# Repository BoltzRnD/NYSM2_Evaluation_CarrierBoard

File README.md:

# NYSM.2 Evaluation Carrier Board

### Note - This repository hosts the design files for the evaluation carrier board only, to explore the NYSM.2 Stepper Driver module please refer to NYSM.2 repository here -
<a href="https://github.com/BoltzRnD/NYSM2_Open_Stepper_Standard">NYSM.2 Open Modular Stepper Driver Interface Standard by Boltz R&D </a>
</br>

### Join our Discord Server to Discuss NYSM.2 -

# NYSM.2 Open Stepper Standard
## Not Your Standard M.2
### "Not Your Standard M.2" is literally not your standard m.2 interface, and is a new open-source stepper motor driver board that utilizes the M.2 interface to control motors using the TMCxx and all other stepper drivers.

Modular stepper drivers are far superior than traditional pololu footprints as it has

1. Poka-yoke installations: The Key's in the interfaces makes sure that you never mess up installation orientations of the driver

apart from this NYSM.2 extends beyond these to provide more features as below:

1. physical locking mechanisms: to make sure drivers are locked in when In operation.

2. Horizontal installation: instead of vertical mounting, to not only save space in Z axis, but to also make the system less fragile to accidental damage if stuck by a physical shock.

3. Top and Bottom Installations: since NYSM.2 utilizes SMD and single layer mounted connectors, it means that it is possible to add by design 2 NYSM.2 modules in the same footprint area, drastically reducing the required footprint for more drivers - i.e - 20 drivers in 10 drivers area by installing 10 on top layer and 10 on bottom.

4. highly cost effective: since M.2 is a widely available standard with high MOQs already flooding the industry, the M.2 connectors can be integrated at very low costs into your design, where the stepper card doesn't even need a connector as it uses an edge connector built into the PCB only. in comparison to other modular standards that uses custom repurposed obsolete connector that has low manufacturing volumes. With NYSM.2 we can adopt a modular standard at almost same cost of a traditional pololu stepper drivers.

5. Powerful in terms of power: NYSM.2 utilizes 8 contacts(0.5A per pin) per power connection to deliver a whopping **4A** to the motors, that too at **24V**, that totals to **96W** per driver.
moreover it is theoretically possible to get more power out of it by increasing the voltages.

But that is not the best thing about NYSM.2 standard, the only best thing about it is only and only it's open source nature and GPL V3 license, that allows creators, hobbyist and manufacturers worldwide to move to a new and open modular stepper driver interface standard.
unlike other modular stepper interfaces, this interface is open inside out, and is not designed to lock you into single specific manufacturer's ecosystem. and is made for the world to use.

## The NYSM.2 Standard Pinout Format

## Pinout Table

| Pin Name   | Pin Number | Description                             
|------------|------------|-----------------------------------------|
| EN         | 1          | Enable/Disable Stepper Driver
| MS1        | 3          | Microstep Selection Pin 1 / CFG1 / SDI
| MS2        | 5          | Microstep Selection Pin 2 / CFG2 / SCK
| UART_TX    | 7          | UART Transmission (Communication) / CFG 3 / CS
| UART_RX    | 9          | UART Receive (Communication) / CFG0 / SDO
| CLK        | 11          | CLK input       
| STEP       | 21          | STEP input            
| DIR        | 23          | DIR input 
| GND        | 25          | Ground                   
| VCC_IO     | 27         | 3.3V to 5V IO supply voltage for all digital pins (does not supply IC logic part).
| GND        | 29         | Ground               
| VREF       | 31         | Analog reference voltage for current scaling or reference current for use of internal sense resistors
| DIAG       | 33         | Diagnostic and StallGuard output
| INDEX      | 35         | Configurable index output. Provides index pulse.
| SPREAD     | 37         | Chopper mode selection: Low=StealthChop, High=SpreadCycle (may be left unconnected)
| STDBY      | 39         | STANDBY input  
| GND        | 45, 47, 49, 51, 53, 55, 57, 59 | Ground/PSU Negative (0.5A per pin, 4A Total)
| POW_MOT    | 61, 63, 65, 67, 69, 71, 73, 75 | Motor supply voltage (0.5A per pin, 4A Total)
| A2         | 4, 6, 8, 10, 20, 22, 24, 26 | Motor coil A output 2 (0.5A per pin, 4A Total)
| A1         | 28, 30, 32, 34, 36, 38, 40, 42 | Motor coil A output 1 (0.5A per pin, 4A Total)
| B1         | 44, 46, 48, 50, 52, 54, 56, 58 | Motor coil B output 1 (0.5A per pin, 4A Total)
| B2         | 60, 62, 64, 66, 68, 70, 72, 74 | Motor coil B output 2 (0.5A per pin, 4A Total)

# Manufacturing and other design considerations

Please take special care to follow these points when manufacturing the NYSM2 Boards
1. You'll need Connector assemblies to interface the board specifically - GHR-06V-S and 511630400 Connectors, which are the same cables used in SmartPrintCoreH7x, please refer to Connector BOM from SmartPrintCoreH7x for more details
2. Set the solder jumpers as per your convenience especially for uart lines, just like your regular pololu drivers, please feel free to browse schematics for reference or directly reach out to our discord server for help.

# License
NYSM.2 standard pinout and NYSM.2 TMC2209 Carrier Board contributed by Boltz R&D is licensed under GPL V3, and is owned by the community and everyone.
Also while the standard is open(i.e - The standard pinout sequence on M.2 Key B and it's derivatives only, that means proprietary manufacturers needs to be compliant to GPLV3 for only the pinout.),
you can integrate it into your proprietary designs as long as the NYSM.2 section of your design respects the license.
We invite all creators, hobbyist, and manufacturers to utilize the standard and the design.

# Key Features for this NYSM.2 Carrier Board:
* NYSM.2 Interface: Compact, modular design that fits into M.2 slots, making it easy to install and maintain.
* The Connectors and pinouts used in the design plugs directly into Smartmotor ports and any SPI Port of SmartPrintCoreH7x, and with just minor pinout configurations in the firmware, it's up and running.

## Assembly and Setup

1. **Step 1**: Insert the **NYSM.2** board into the M.2 slot.
2. **Step 2**: Connect your stepper motor wires to the appropriate output terminals i.e- Smartmotor ports and any spi port(which can also act as a uart port).
3. **Step 3**: Configure your firmware (e.g., **Marlin** or **Klipper**) to control the TMC2209 driver.
4. **Step 4**: Power on the system, and your motors are ready.

## Getting Started on Development:

Clone the repository:  
`git clone https://github.com/BoltzRnD/NYSM2_Evaluation_CarrierBoard`

# Join the Community
We are actively looking for contributors to help us enhance this project. You can join our community to discuss ideas, report bugs, or request features:

- **Discord**: [Join us here](https://discord.gg/xWGaHd83Hs)
- **Email**: info@boltzrnd.com

# Future Plans
- **Custom Heatsink Designs**.
- **Extended Compatibility**: support for other stepper driver like TMC5160 and TMC2130.

# Disclaimer
The **NYSM.2 standard and NYSM.2 Carrier board** is provided as-is without any warranties. Boltz R&D is not responsible for any damages or issues that may arise from the use of this board.

    NYSM.2 standard
    Copyright (C) 2024 Boltz R&D

    This Project/Open Standard is free: you can redistribute it and/or modify
    it under the terms of the GNU General Public License as published by
    the Free Software Foundation, either version 3 of the License, or
    (at your option) any later version.

    This is distributed in the hope that it will be useful,
    but WITHOUT ANY WARRANTY; without even the implied warranty of
    MERCHANTABILITY or FITNESS FOR A PARTICULAR PURPOSE.  See the
    GNU General Public License for more details.

    You should have received a copy of the GNU General Public License
    along with this program.  If not, see <https://www.gnu.org/licenses/>.

Contact : info@boltzrnd.com

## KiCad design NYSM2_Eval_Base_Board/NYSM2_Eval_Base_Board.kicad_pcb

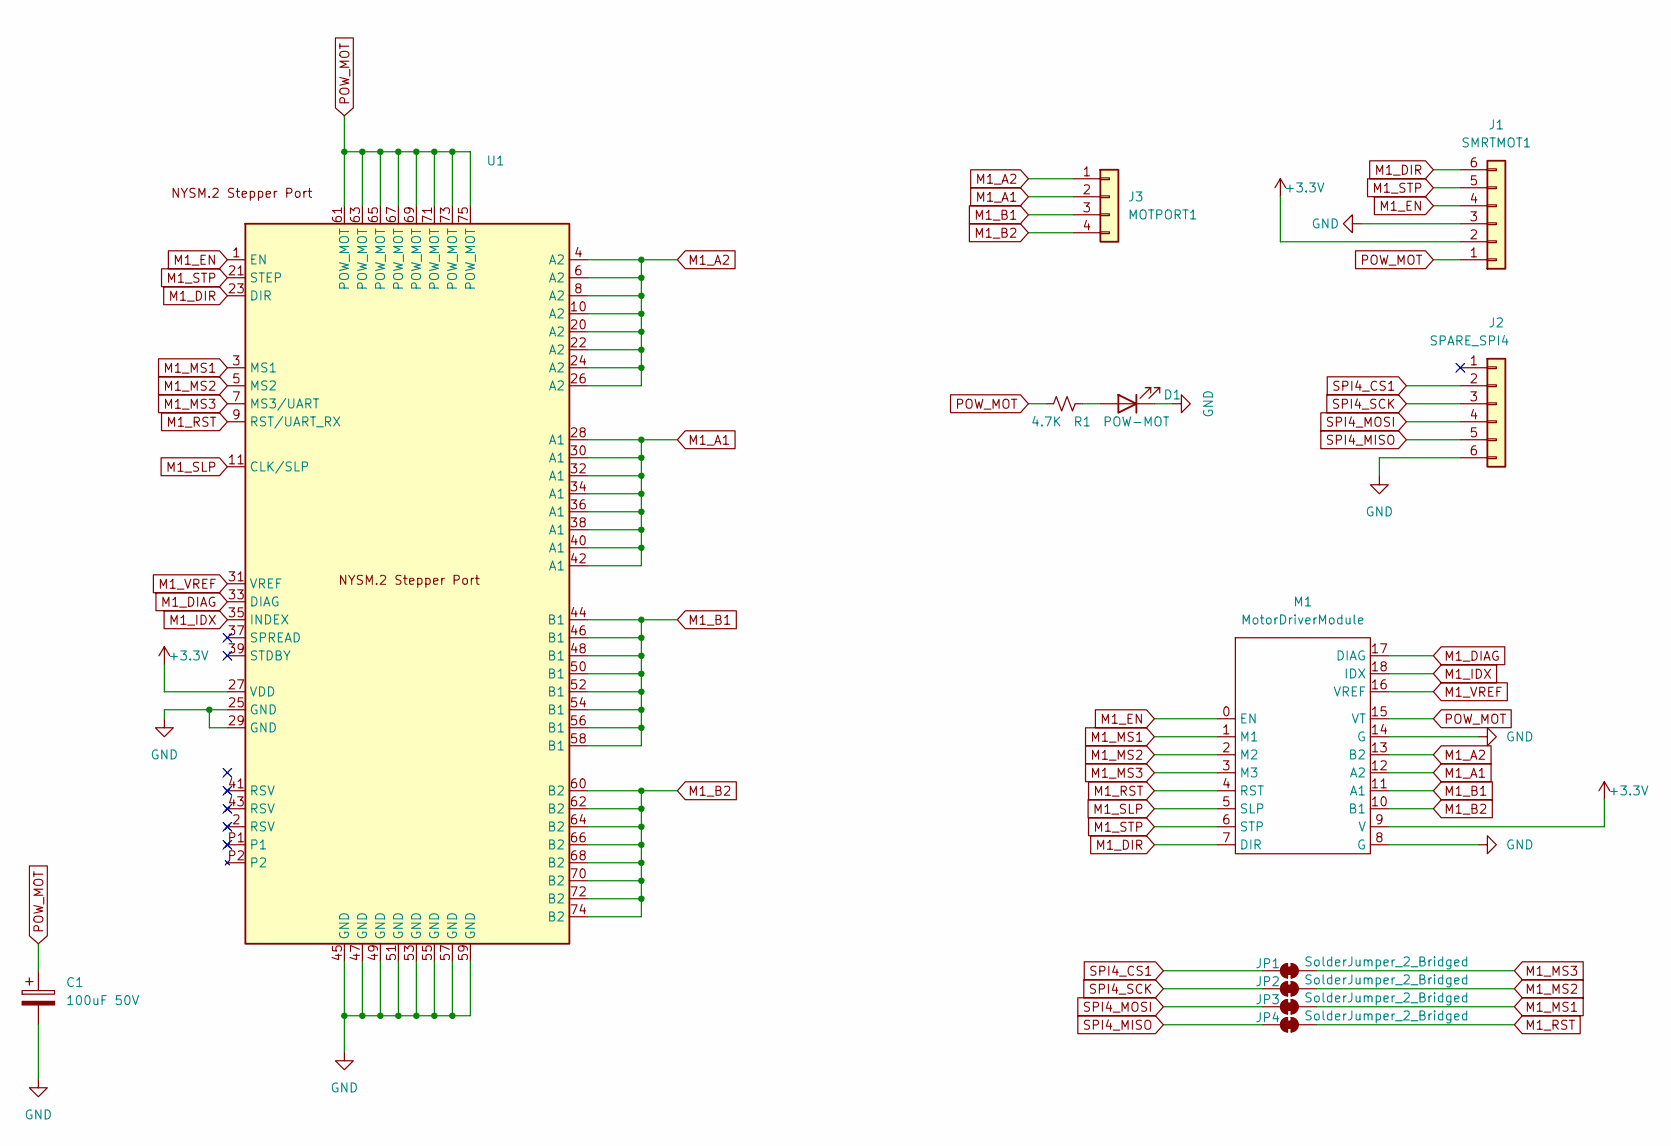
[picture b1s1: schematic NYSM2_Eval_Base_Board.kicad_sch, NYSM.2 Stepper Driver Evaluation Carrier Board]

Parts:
C1: 100uF 50V; C_Radial_D8.0mm_H11.5mm_P3.50mm
D1: POW-MOT; LED_0603_1608Metric; Manufacturer_Part_Number B1911PG--20D000514U1930
J1: SMRTMOT1; 53375-0610; Manufacturer_Part_Number 53375-0610
J2: SPARE_SPI4; JST_GH_BM06B-GHS-TBT_1x06-1MP_P1.25mm_Vertical; Manufacturer_Part_Number BM06B-GHS-TBT
J3: MOTPORT1; 53375-0410; Manufacturer_Part_Number 53375-0410
JP1, JP2, JP3, JP4: SolderJumper_2_Bridged; SolderJumper-2_P1.3mm_Bridged_RoundedPad1.0x1.5mm
M1: MotorDriverModule; MotorDriverModuleBase
R1: 4.7K; R_0402_1005Metric; Manufacturer_Part_Number CRGCQ0402J4K7
U1: AMPHENOL_MDT275B03001; Manufacturer_Part_Number AS0BC21-S30BB-7H

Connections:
+3.3V: J1.2, M1.9 (V), U1.27 (VDD)
GND: C1.2, D1.1 (K), J1.3, J2.6, M1.8 (G), M1.14 (G), U1.25 (GND), U1.29 (GND), U1.45 (GND), U1.47 (GND), U1.49 (GND), U1.51 (GND), U1.53 (GND), U1.55 (GND), U1.57 (GND), U1.59 (GND)
M1_A1: J3.2, M1.12 (A2), U1.28 (A1), U1.30 (A1), U1.32 (A1), U1.34 (A1), U1.36 (A1), U1.38 (A1), U1.40 (A1), U1.42 (A1)
M1_A2: J3.1, M1.13 (B2), U1.4 (A2), U1.6 (A2), U1.8 (A2), U1.10 (A2), U1.20 (A2), U1.22 (A2), U1.24 (A2), U1.26 (A2)
M1_B1: J3.3, M1.11 (A1), U1.44 (B1), U1.46 (B1), U1.48 (B1), U1.50 (B1), U1.52 (B1), U1.54 (B1), U1.56 (B1), U1.58 (B1)
M1_B2: J3.4, M1.10 (B1), U1.60 (B2), U1.62 (B2), U1.64 (B2), U1.66 (B2), U1.68 (B2), U1.70 (B2), U1.72 (B2), U1.74 (B2)
M1_DIAG: M1.17 (DIAG), U1.33 (DIAG)
M1_DIR: J1.6, M1.7 (DIR), U1.23 (DIR)
M1_EN: J1.4, M1.0 (EN), U1.1 (EN)
M1_IDX: M1.18 (IDX), U1.35 (INDEX)
M1_MS1: JP3.2 (B), M1.1 (M1), U1.3 (MS1)
M1_MS2: JP2.2 (B), M1.2 (M2), U1.5 (MS2)
M1_MS3: JP1.2 (B), M1.3 (M3), U1.7 (MS3/UART)
M1_RST: JP4.2 (B), M1.4 (RST), U1.9 (RST/UART_RX)
M1_SLP: M1.5 (SLP), U1.11 (CLK/SLP)
M1_STP: J1.5, M1.6 (STP), U1.21 (STEP)
M1_VREF: M1.16 (VREF), U1.31 (VREF)
unnamed: D1.2 (A), R1.1
POW_MOT: C1.1, J1.1, M1.15 (VT), R1.2, U1.61 (POW_MOT), U1.63 (POW_MOT), U1.65 (POW_MOT), U1.67 (POW_MOT), U1.69 (POW_MOT), U1.71 (POW_MOT), U1.73 (POW_MOT), U1.75 (POW_MOT)
SPI4_CS1: J2.2, JP1.1 (A)
SPI4_MISO: J2.5, JP4.1 (A)
SPI4_MOSI: J2.4, JP3.1 (A)
SPI4_SCK: J2.3, JP2.1 (A)

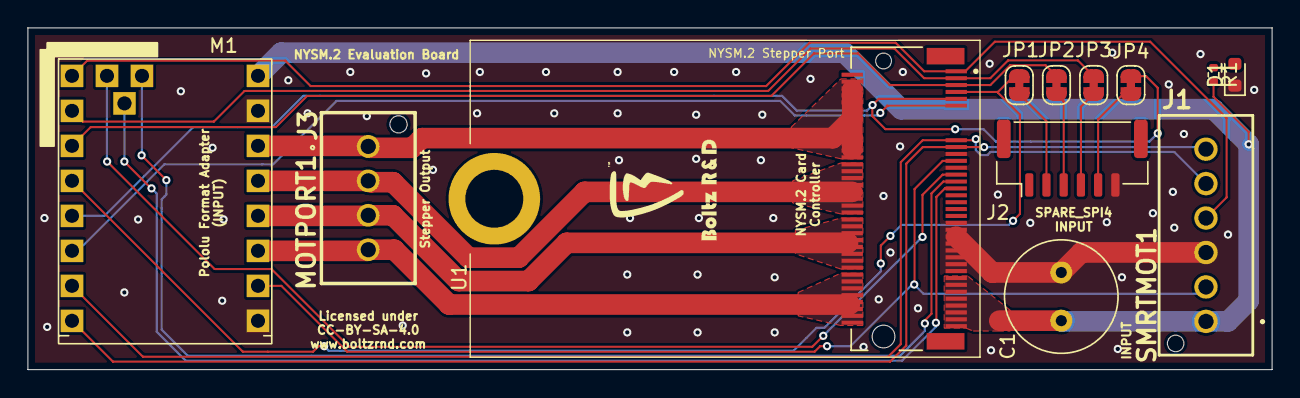
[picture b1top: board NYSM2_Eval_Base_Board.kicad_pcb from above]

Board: 2 copper layers, 90.3 x 24.8 mm, 12 parts (0 on the bottom side), 23 nets.

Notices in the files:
NYSM2_Eval_Base_Board/NYSM2_Eval_Base_Board.kicad_pcb:
CC-BY-SA-4.0
